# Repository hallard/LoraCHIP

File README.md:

C.H.I.P. Computer Lora Gateway/Node for RFM95 or RN2483 Modules
===============================================================

This shield is used to hold HopeRF [Lora module][4] or Microchip [RN2483 LoraWan modules][3] Software with $9 [C.H.I.P. Computer][5]. it has just few minimal features. 

This shield can also act as a LoraWAN Node/gateway using this custom dedicated software    
- C.H.I.P. version of [LMIC][9] stack. This LMIC is in progress to works with this shield.

Features
========
- Footprint for RFM92/95/96/98 Lora module or Microchip RN2483 module
- Placement for choosing single Wire, SMA or u-FL Antenna type
- 2 x LED LED for visual indication
- 1 x Switch button (for example to power clean power off CHIP)
- I2C connector to connect 128x64 Oled or I2C sensors
- FTDI connector connected to Uart2 or Uart1 (selectable with a switch)

I'm waiting now for V1.0 boards PCBs.io, so I didn't fully tested them, I will update ASAP.

Detailed Description
====================

Look at the schematics for more informations.

For RFM95 SPI connexion is classic (MOSI/MISO/CLK/CS) is for SPI2 of CHIP Computer.

Only One GPIO needed for DIO0/DIO1/DIO2 (OR made with 3 diodes and one resistor R3) that will make this board fully compatible with current LIMC implementation, even if I've done a software fix which works with no interrupt. Only Needed for Lora modules, if you're using RFM69HCW and and to use IRQ just place D0 and R3.

Detailed Description
====================

On board switch select which Uart goes to FTDI connector (Uart1 or Uart2), RN2483 use CHIP UART2 and leave you UART1 to connect with serial console to CHIP with FTDI cable.

You can also use shield as a standalone RN2483, just plug FTDI connector with decent 3V3 supply, best us to use FTDI cable with 3V3/5V selectable power (select 3V3 of course)

Please look at C.H.I.P. [Hardware documentation][6].

```
CHIP Computer        RN2483
   LCD-D7        <---->  Reset
   LCD-D2 (TXD2) <---->  RXD
   LCD-D3 (RXD2) <---->  TXD

CHIP Computer    RFM95 Module
   CSIPCK   <---->  CS
   CSICK    <---->  CLK
   CSIHSYNC <---->  MOSI
   CSIVSYNC <---->  MISO
   CSID3    <---->  Reset
   DIO0     <---->  CSID0
   DIO1     <---->  CSID1
   DIO2     <---->  CSID2

CHIP Computer   On Board Leds
   LCD-D4  <---->  RED LED
   PWM     <---->  GREEN LED
```

### Schematic  

### Boards  

You can order the PCB of this board at [PCBs.io][8]. PCBs.io give me some reward when you order my designed boards from their site. This is pretty good, because I can use these rewards to create and design new boards and order boards for a discounted price and share new boards. So if you don't care about PCB manufacturer please use PCBs.io.

### Assembled boards (V1.0)

TBD

### V1.0 connected to C.H.I.P.

TBD

##License

This work is licensed under a [Creative Commons Attribution-NonCommercial 4.0 International License](http://creativecommons.org/licenses/by-nc/4.0/)    
If you want to do commercial stuff with this project, please contact [CH2i company](https://www.ch2i.eu/en#support) so we can organize an simple agreement.

##Misc

See news and other projects on my [blog][2] 

[1]: https://staging.thethingsnetwork.org/wiki/Hardware/Gateways/DIY 
[2]: https://hallard.me
[3]: http://www.microchip.com/wwwproducts/en/RN2483
[4]: http://www.hoperf.com/rf_transceiver/lora/
[5]: https://getchip.com/pages/chip
[6]: https://docs.getchip.com/chip.html#pin-headers
[8]: https://PCBs.io/share/46N5m
[9]: https://github.com/hallard/arduino-lmic/tree/rpi
[13]: https://github.com/hallard/arduino-lmic/blob/rpi/README.md

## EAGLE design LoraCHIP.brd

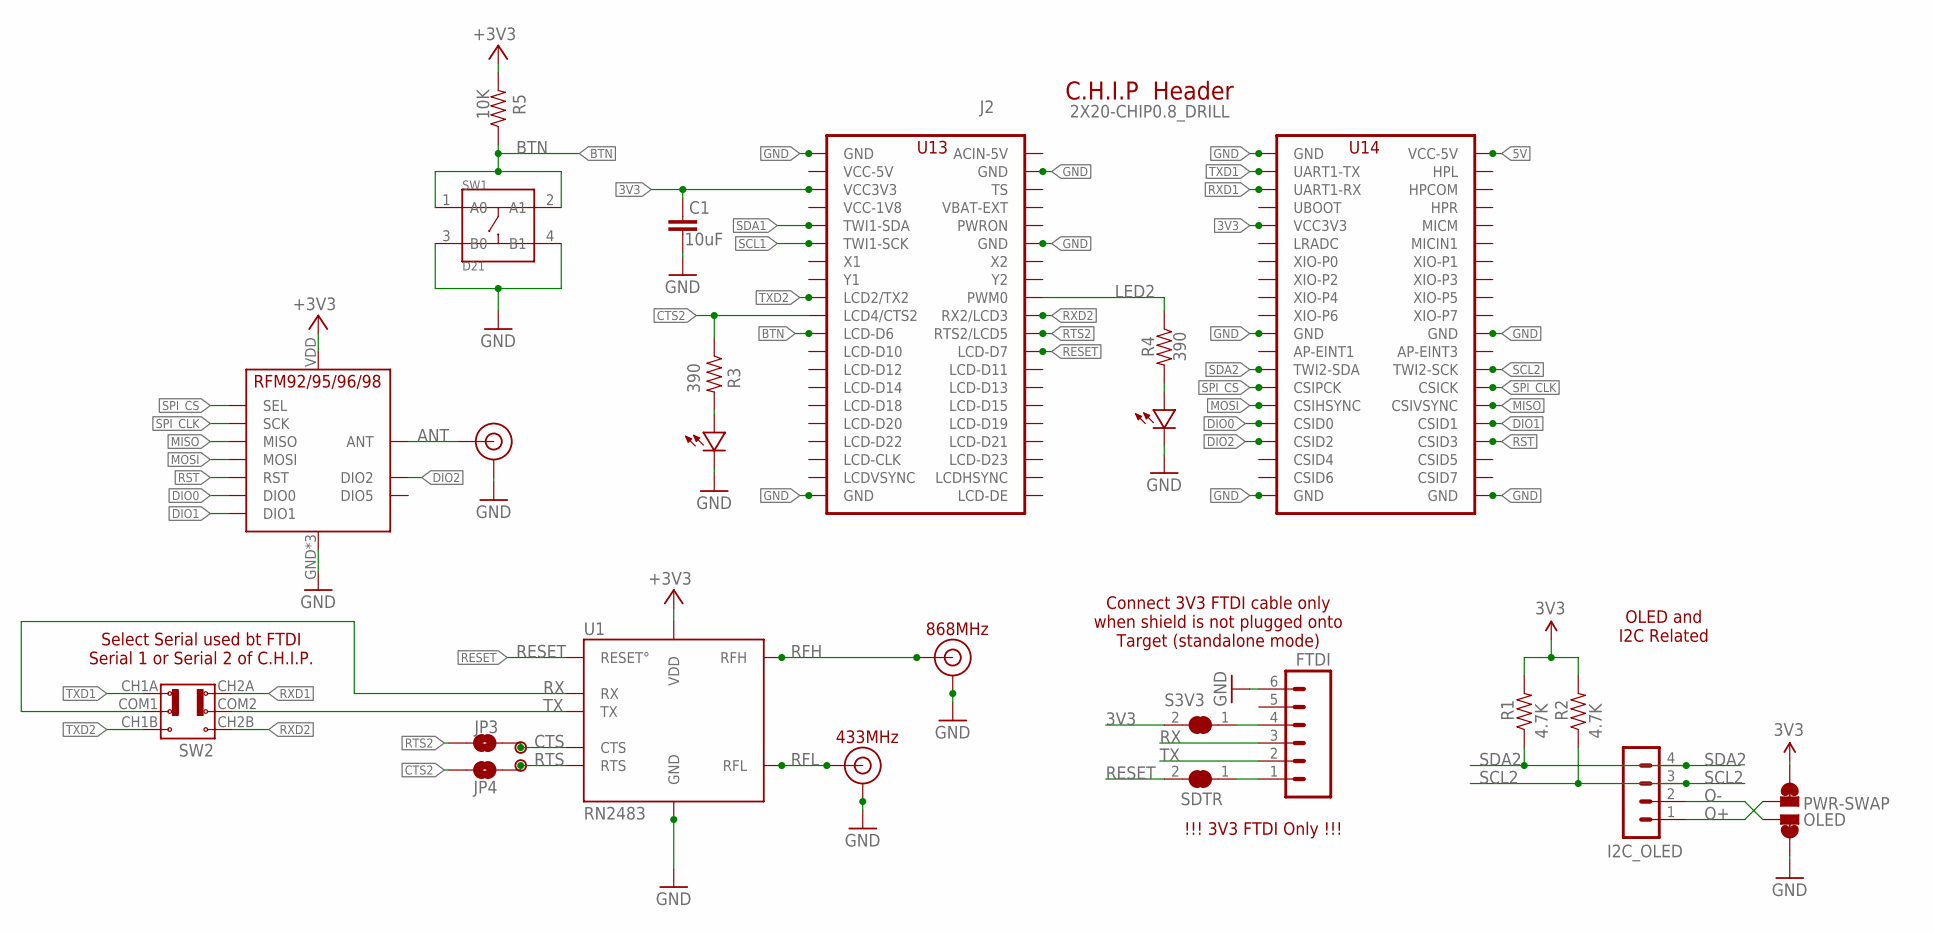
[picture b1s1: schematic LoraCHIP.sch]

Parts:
C1: 10uF; 0805-CAP-LARGEPADS
FTDI: M06SIP; 1X06
I2C_OLED: CON_HEADER_1X04'SMALL''; M1X4
J2: 2X20-CHIP0.8_DRILL; 2X20CHIP_NOOFFSET-TH_0.8
J$1, J$2, J$3: ANTENNATINY; SMA_UFL_PAD_TINY
JP3: CTS; PAD-JUMPER-2-NO_YES_SILK
JP4: RTS; PAD-JUMPER-2-NO_YES_SILK
OLED: PWR-SWAP; PAD-JUMPER-SWAP
P1, P2: PADSMALL; PAD-SMALL
R1, R2: 4.7K; 0805-RES
R3, R4: 390; 0805-RES
R5: 10K; 0805-RES
S3V3: SOLDERJUMPER_CLOSED; SOLDERJUMPER_CLOSEDWIRE
SDTR: SOLDERJUMPER_CLOSED; SOLDERJUMPER_CLOSEDWIRE
SW1: D21; SW4-SMD-4.2X3.2X2.5MM
SW2: SWITCH-2CH-6P-3010010P1; 6P-2CH-2.54-9.1X3.5X3.2+2H
U1: RN2483; RN2483_NOGPIO
U$1: GRN; 0805-LED
U$3: RED; 0805-LED
U$4: RFM95

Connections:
3V3: C1.2, J2.VCC3V3, J2.VCC3V3@1 (VCC3V3), OLED.4, OLED.44 (4), R1.2, R2.2, R5.2, S3V3.2, U1.VDD, U1.VDD2 (VDD), U$4.VDD (VCC)
5V: J2.VCC5V@1 (VCC-5V)
ANT: J$3.ANT0 (ANT), J$3.ANT1 (ANT), J$3.ANT2 (ANT), U$4.ANT
BTN: J2.LCD-D6, R5.1, SW1.1 (A0), SW1.2 (A1)
CTS: JP3.1, P1.1, U1.UART_CTS (CTS)
CTS2: J2.LCD-D4 (LCD4/CTS2), JP4.2, R3.1
DIO0: J2.CSID0, U$4.DIO0
DIO1: J2.CSID1, U$4.DIO1
DIO2: J2.CSID2, U$4.DIO2
GND: C1.1, FTDI.6, J2.GND@1 (GND), J2.GND@2 (GND), J2.GND@3 (GND), J2.GND@4 (GND), J2.GND@5 (GND), J2.GND@6 (GND), J2.GND@7 (GND), J2.GND@8 (GND), J2.GND@10 (GND), J$1.GND1 (GND), J$1.GND2 (GND), J$1.GND3 (GND), J$1.GND4 (GND), J$1.GND5 (GND), J$1.GND6 (GND), J$2.GND1 (GND), J$2.GND2 (GND), J$2.GND3 (GND), J$2.GND4 (GND), J$2.GND5 (GND), J$2.GND6 (GND), J$3.GND1 (GND), J$3.GND2 (GND), J$3.GND3 (GND), J$3.GND4 (GND), J$3.GND5 (GND), J$3.GND6 (GND), OLED.1, OLED.11 (1), SW1.3 (B0), SW1.4 (B1), U1.GND, U1.GND1 (GND), U1.GND2 (GND), U1.GND3 (GND), U1.GND4 (GND), U1.GND5 (GND), U1.GND6 (GND), U1.GND7 (GND), U1.GND8 (GND), U1.GND9 (GND), U1.GND10 (GND), U1.GND11 (GND), U1.GND12 (GND), U$1.MINUS, U$3.MINUS, U$4.GND, U$4.GND1 (GND), U$4.GND2 (GND)
LD2: R4.2, U$1.PLUS
LED2: J2.PWM0, R4.1
MISO: J2.CSIVSYNC, U$4.MISO
MOSI: J2.CSIHSYNC, U$4.MOSI
unnamed: FTDI.1, SDTR.1
unnamed: FTDI.4, S3V3.1
unnamed: R3.2, U$3.PLUS
O+: I2C_OLED.1, OLED.3
O-: I2C_OLED.2, OLED.2
RESET: J2.LCD-D7, SDTR.2, U1.RESET°
RFH: J$2.ANT0 (ANT), J$2.ANT1 (ANT), J$2.ANT2 (ANT), U1.RFH
RFL: J$1.ANT0 (ANT), J$1.ANT1 (ANT), J$1.ANT2 (ANT), U1.RFL
RST: J2.CSID3, U$4.RST
RTS: JP4.1, P2.1, U1.UART_RTS (RTS)
RTS2: J2.LCD-D5 (RTS2/LCD5), JP3.2
RX: FTDI.3, SW2.COM1, U1.UART_RX (RX)
RXD1: J2.UART1-RX, SW2.CH2A
RXD2: J2.LCD-D3 (RX2/LCD3), SW2.CH2B
SCL1: J2.TWI1-SCK
SCL2: I2C_OLED.3, J2.TWI2-SCK, R2.1
SDA1: J2.TWI1-SDA
SDA2: I2C_OLED.4, J2.TWI2-SDA, R1.1
SPI_CLK: J2.CSICK, U$4.SCK
SPI_CS: J2.CSIPCK, U$4.NSS (SEL)
TX: FTDI.2, SW2.COM2, U1.UART_TX (TX)
TXD1: J2.UART1-TX, SW2.CH1A
TXD2: J2.LCD-D2 (LCD2/TX2), SW2.CH1B
VCC-1V8: J2.VCC1V8 (VCC-1V8)
VCC-5V: J2.VCC5V@0 (VCC-5V)

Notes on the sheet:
C.H.I.P Header
868MHz
433MHz
Connect 3V3 FTDI cable only when shield is not plugged onto Target (standalone mode)
!!! 3V3 FTDI Only !!!
OLED and I2C Related
Select Serial used bt FTDI Serial 1 or Serial 2 of C.H.I.P.

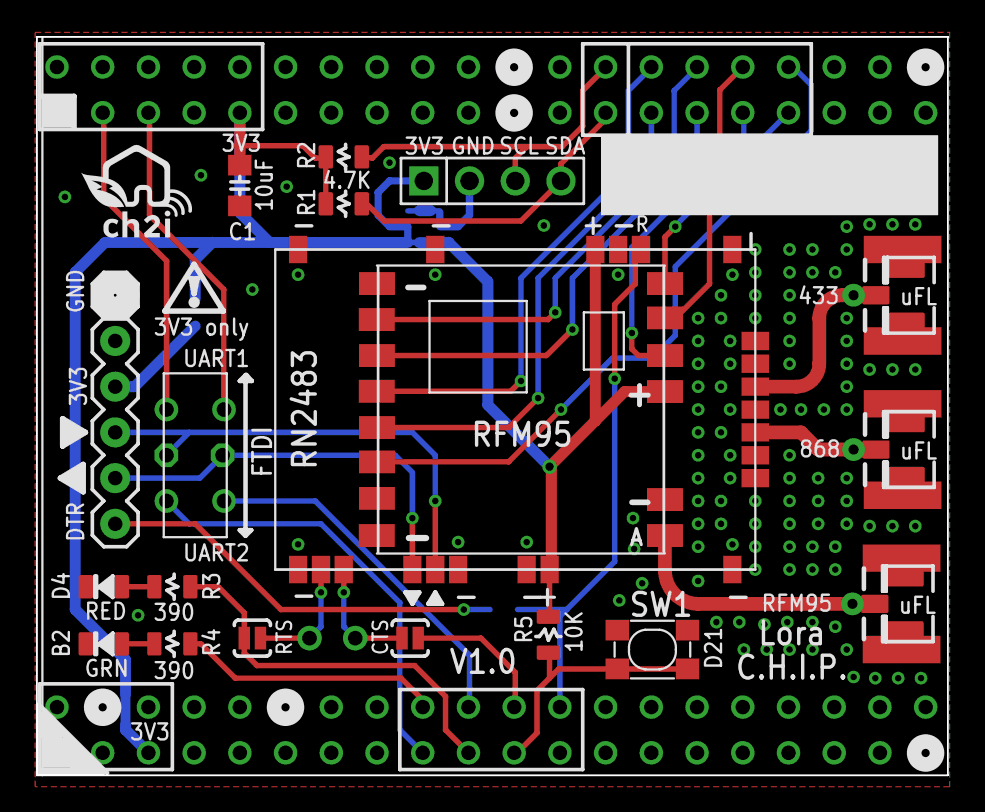
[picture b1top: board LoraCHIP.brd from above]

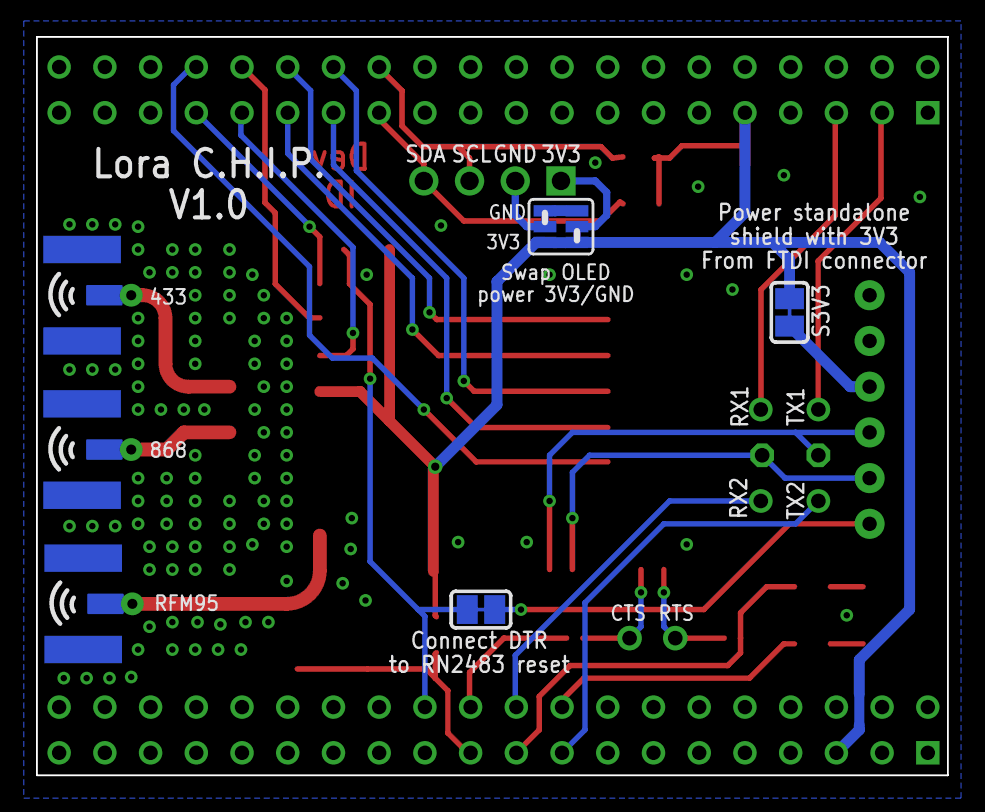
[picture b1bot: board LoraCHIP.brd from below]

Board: 2 copper layers, 50.6 x 41.0 mm, 26 parts (3 on the bottom side), 34 nets.

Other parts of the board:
U$2: LOGO_C2I_015

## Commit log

2017-01-13 :neckbeard: Added .gitattributes
2017-01-13 Creation
2017-01-13 Added CHIP link
2017-01-13 Added Chip Hardware Link

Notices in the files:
parts and their libraries:
microbuilder: This work is placed in the public domain, and may be freely used for commercial and non-commercial work with the following conditions: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
SparkFun-Passives: Licensing: Creative Commons ShareAlike 4.0 International - https://creativecommons.org/licenses/by-sa/4.0
